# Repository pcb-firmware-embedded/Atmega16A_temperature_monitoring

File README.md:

# ATmega16A Temperature Monitoring and Alarm System

## Project Overview

This repository contains the complete development of a temperature monitoring and alarm system based on the **ATmega16A** microcontroller.

The project includes:

- Firmware development in Atmel Studio
- Circuit simulation in Proteus
- Schematic capture in KiCad
- PCB layout and 3D visualization
- Bluetooth communication
- LCD interface
- DHT11 temperature & humidity sensing
- Relay, buzzer and warning LED control

---

# Firmware Development (Atmel Studio)

The firmware was written in Embedded C using Atmel Studio.

---

# Proteus Simulation

The complete system was verified in Proteus before manufacturing the PCB.

---

# KiCad Schematic

The schematic integrates:

- ATmega16A
- DHT11
- Bluetooth module
- LCD
- Relay
- Buzzer
- LED
- Power supply

---

# PCB Design

The PCB was designed in KiCad with attention to routing, grounding and component placement.

---

## Project Workflow

```text
Firmware Development
        ↓
Proteus Simulation
        ↓
KiCad Schematic
        ↓
PCB Layout
        ↓
Hardware Manufacturing
        ↓
Testing
```

## Technologies

- ATmega16A
- Embedded C
- Atmel Studio
- KiCad
- Proteus
- DHT11
- LCD1602
- UART Bluetooth

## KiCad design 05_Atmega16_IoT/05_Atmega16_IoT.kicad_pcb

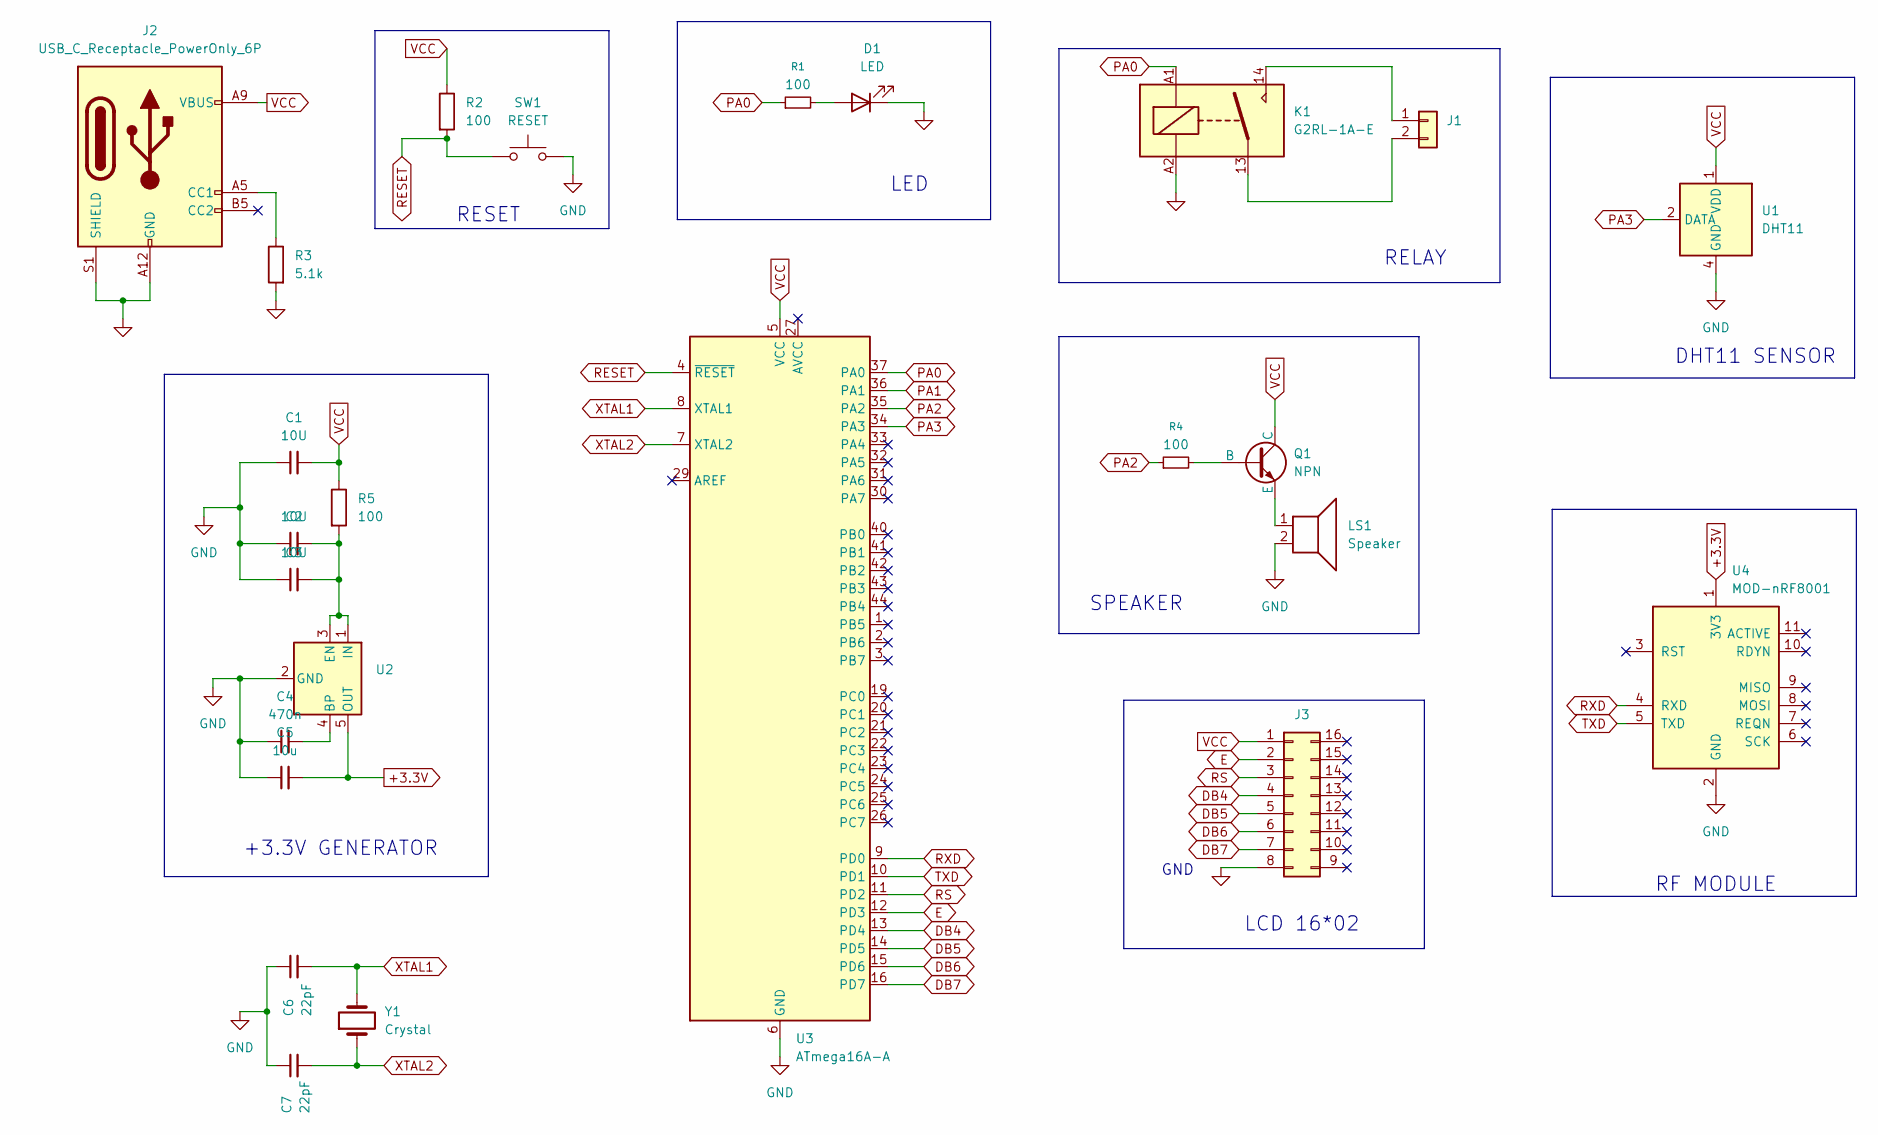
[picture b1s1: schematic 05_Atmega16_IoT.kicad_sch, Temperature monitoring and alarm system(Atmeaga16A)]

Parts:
C1, C2, C3: 10U; C_0805_2012Metric_Pad1.18x1.45mm_HandSolder
C4: 470n; C_0805_2012Metric_Pad1.18x1.45mm_HandSolder
C5: 10u; C_0805_2012Metric_Pad1.18x1.45mm_HandSolder
C6, C7: 22pF; C_0805_2012Metric_Pad1.18x1.45mm_HandSolder
D1: LED; LED_1206_3216Metric
J1: Conn_01x02; TerminalBlock_RND_205-00232_1x02_P5.08mm_Horizontal
J2: USB_C_Receptacle_PowerOnly_6P; USB_C_Receptacle_GCT_USB4125-xx-x_6P_TopMnt_Horizontal
J3: Conn_02x08_Counter_Clockwise; PinSocket_2x08_P2.54mm_Vertical
K1: G2RL-1A-E; Relay_SPST_Omron_G2RL-1A-E
LS1: Speaker; Speaker_CUI_CMR-1206S-67
Q1: NPN; TO-92
R1, R4: 100; R_0402_1005Metric
R2, R5: 100; R_1206_3216Metric
R3: 5.1k; R_1206_3216Metric
SW1: RESET; SW_Tactile_SPST_NO_Straight_CK_PTS636Sx25SMTRLFS
U1: DHT11; Aosong_DHT11_5.5x12.0_P2.54mm
U2: SPX3819M5-L-3-3; SOT-23-5
U3: ATmega16A-A; TQFP-44_10x10mm_P0.8mm
U4: MOD-nRF8001
Y1: Crystal; Crystal_HC52-6mm_Vertical

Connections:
+3.3V: C5.2, U2.5 (OUT), U4.1 (3V3)
DB4: J3.4, U3.13 (PD4)
DB5: J3.5, U3.14 (PD5)
DB6: J3.6, U3.15 (PD6)
DB7: J3.7, U3.16 (PD7)
E: J3.2, U3.12 (PD3)
GND: C1.1, C2.1, C3.1, C4.1, C5.1, C6.1, C7.1, D1.1 (K), J2.A12 (GND), J2.B12 (GND), J2.S1 (SHIELD), J3.8, K1.A2, LS1.2, R3.2, SW1.2, U1.4 (GND), U2.2 (GND), U3.6 (GND), U3.18 (GND), U3.28 (GND), U3.39 (GND), U4.2 (GND)
unnamed: D1.2 (A), R1.2
unnamed: J1.1, K1.14
unnamed: J1.2, K1.13
unnamed: J2.A5 (CC1), R3.1
unnamed: Q1.2 (B), R4.2
unnamed: LS1.1, Q1.3 (E)
unnamed: C4.2, U2.4 (BP)
unnamed: C2.2, C3.2, R5.2, U2.1 (IN), U2.3 (EN)
PA0: K1.A1, R1.1, U3.37 (PA0)
PA1: U3.36 (PA1)
PA2: R4.1, U3.35 (PA2)
PA3: U1.2 (DATA), U3.34 (PA3)
RESET: R2.2, SW1.1, U3.4 (~RESET)
RS: J3.3, U3.11 (PD2)
RXD: U3.9 (PD0), U4.4 (RXD)
TXD: U3.10 (PD1), U4.5 (TXD)
VCC: C1.2, J2.A9 (VBUS), J2.B9 (VBUS), J3.1, Q1.1 (C), R2.1, R5.1, U1.1 (VDD), U3.5 (VCC), U3.17 (VCC), U3.38 (VCC)
XTAL1: C6.2, U3.8 (XTAL1), Y1.2
XTAL2: C7.2, U3.7 (XTAL2), Y1.1

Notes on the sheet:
DHT11 SENSOR
RF MODULE
+3.3V GENERATOR
GND
LCD 16*02
RELAY
RESET
LED
SPEAKER

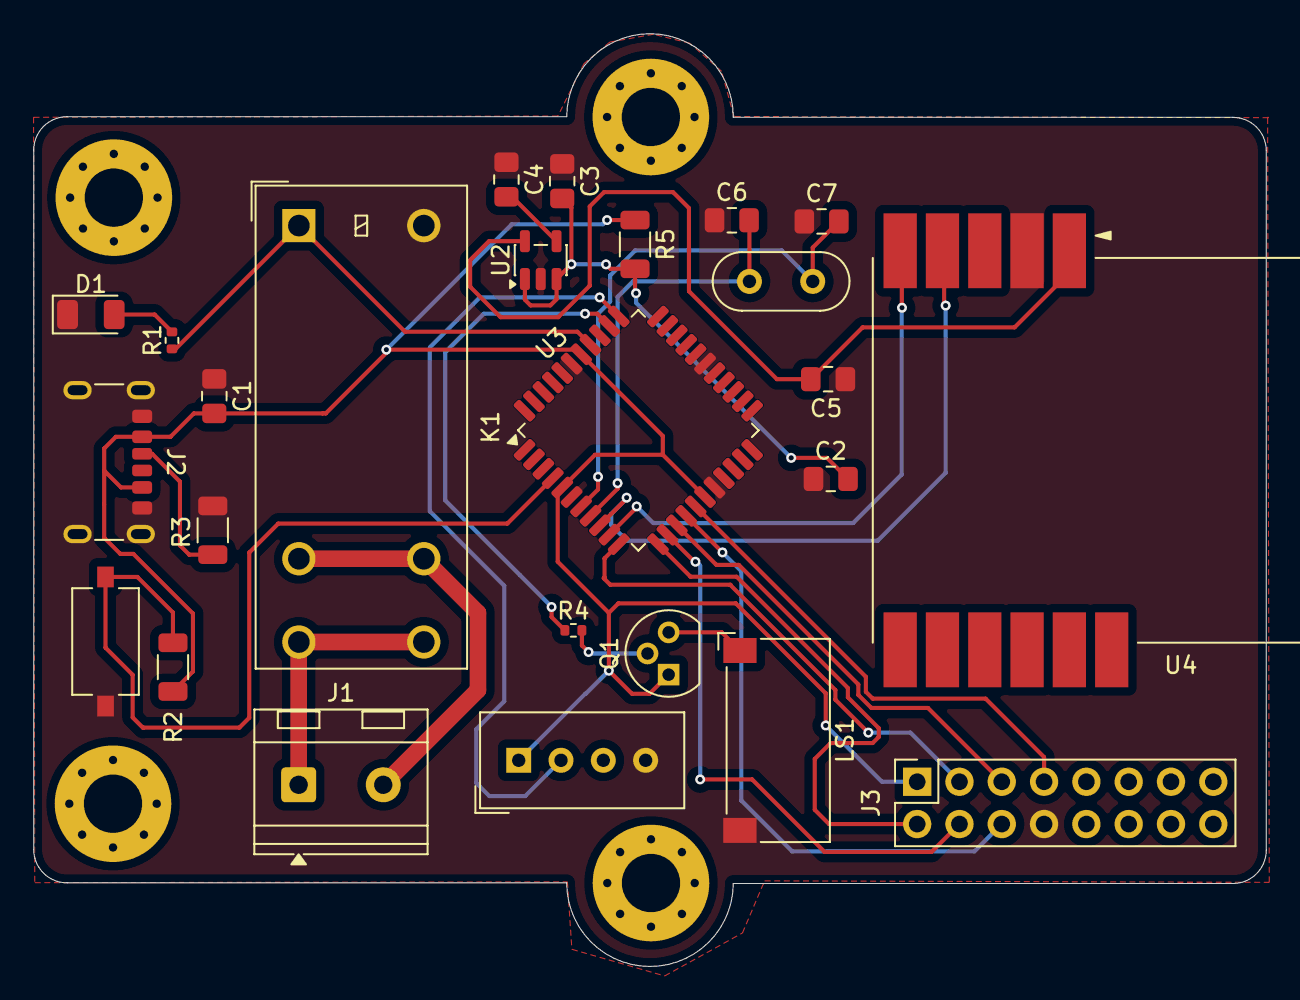
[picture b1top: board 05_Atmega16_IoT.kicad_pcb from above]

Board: 2 copper layers, 74.0 x 56.0 mm, 25 parts (0 on the bottom side), 25 nets.
